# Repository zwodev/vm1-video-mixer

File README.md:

# VM-1 / The Video Mixer for Everyone

The VM-1 is an open-source hardware project for live mixing of videos, camera images and generative graphics. It is based on the widely used and affordable Raspberry Pi (5) platform, allowing creative media projects of all sorts.

Learn more about the VM-1 on our website: [VM-1 Website](https://vm-1.com)

## 🚀 Quick Start

You want to build your very own VM-1?! Awesome! This is how you do it:

### 1. Order the Parts
You're lucky! We've prepared a shopping list for you. This is a link to the shopping cart at BerryBase (Berlin, Germany). You don't have to buy the parts there and this is no affiliate link. It's just for your convenience!
This list includes everything you need. If you already own some parts, just delete them from the cart.

[Shopping List](https://www.berrybase.de/loadBasket/sqdnehV_owC)

### 2. Print your Case
Don't worry, you do not have wildly connect all the parts. We've prepared a neat little housing for your VM-1. You just have to print it on your own, your friend's or your makerspace's 3D-printer. If you have trouble getting your case printed, don't worry and drop us a line.

[3D Printing Files](#)

### 3. Download VM-1 image and flash your SD card
TODO

### 4. Assemble the VM-1
TODO

### 5. First Steps
TODO

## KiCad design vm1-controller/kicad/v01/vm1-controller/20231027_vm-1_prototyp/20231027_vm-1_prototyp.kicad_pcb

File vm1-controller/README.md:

# VM-1 Controller

folders:

`arduino` - latest firmware

`firmware`- was a test and is obsolete

`kicad`- the latest pcb

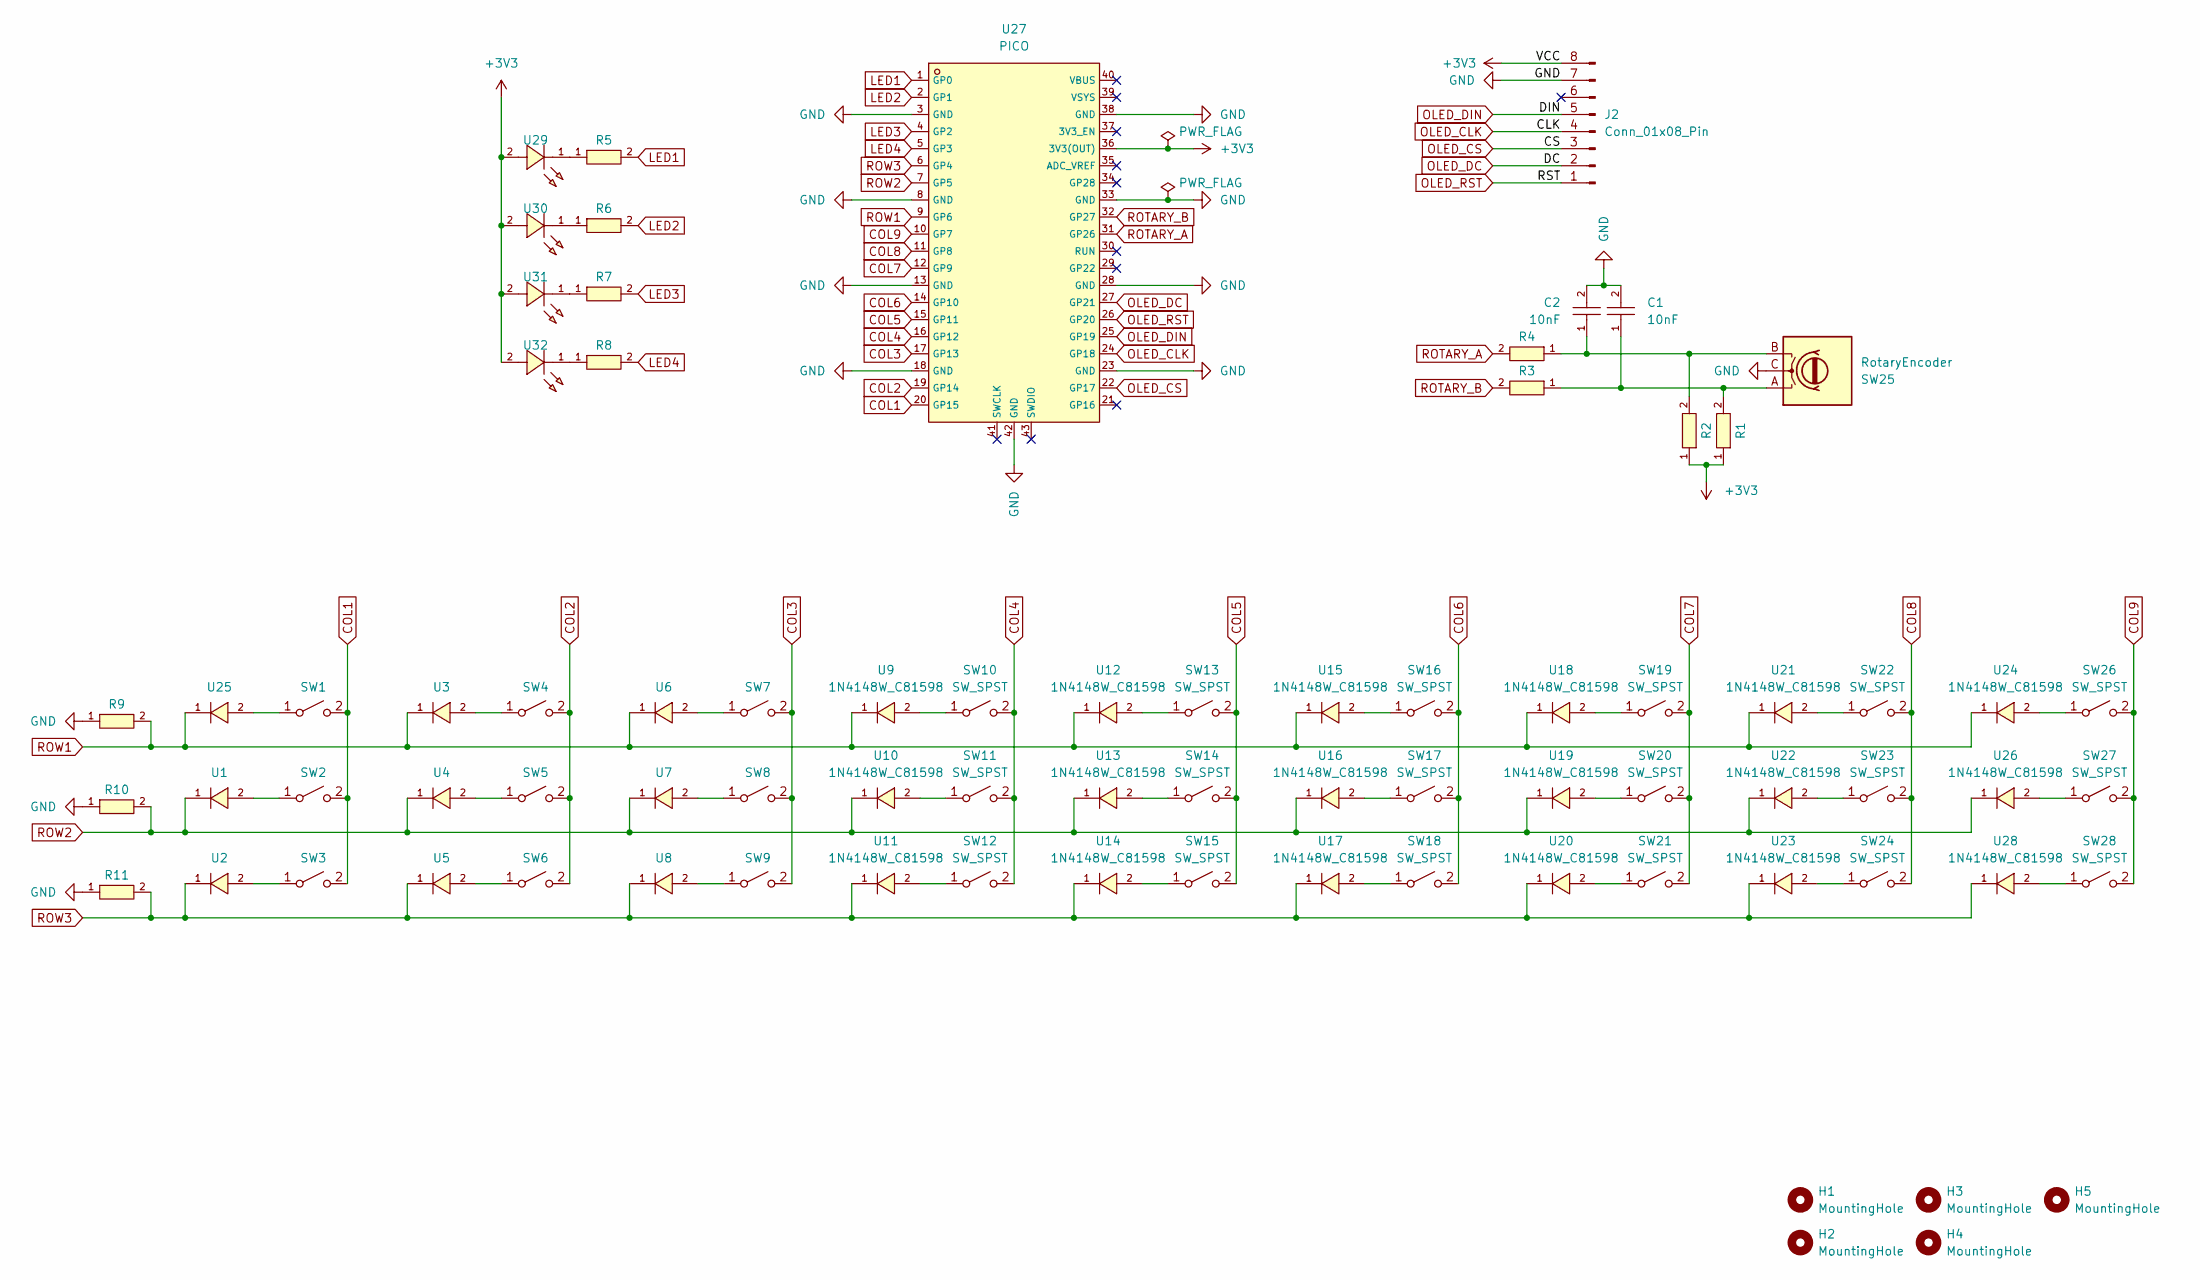
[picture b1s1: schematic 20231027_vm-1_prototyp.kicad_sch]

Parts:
C1, C2: 10nF; C0402; LCSC C15195
H1, H2, H3, H4, H5: MountingHole; MountingHole_3.2mm_M3
J2: Conn_01x08_Pin; Waveshare OLED 1.5in
R1, R2, R9, R10, R11: 0402WGF1002TCE; R0402; LCSC C25744
R3, R4: 0402WGF1002TCE 10k; R0402; LCSC C25744
R5, R6, R7, R8: 0402WGF1000TCE; R0402; LCSC C25076
SW1, SW2, SW3, SW4, SW5, SW6, SW7, SW8, SW9, SW10, SW11, SW12, SW13, SW14, SW15, SW16, SW17, SW18, SW19, SW20, SW21, SW22, SW23, SW24, SW26, SW27, SW28: SW_SPST; SW_Cherry_MX_PCB_1.00u
SW25: RotaryEncoder; RotaryEncoder_Bourns_Vertical_PEC12R-3xxxF-Nxxxx
U1, U2, U3, U4, U5, U6, U7, U8, U9, U10, U11, U12, U13, U14, U15, U16, U17, U18, U19, U20, U21, U22, U23, U24, U25, U26, U28: 1N4148W_C81598; SOD-123F_L2.7-W1.6-LS3.8-RD; LCSC C81598
U27: PICO; COMM-SMD_L51.0-W21.0-P2.54_SC0916; LCSC C7203002
U29, U30, U31, U32: 95-21SURC_S530-A3_TR10; LED-SMD_L2.1-W2.0-RD; LCSC C2936535

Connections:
+3V3: J2.8, R1.1, R2.1, U27.36 (3V3(OUT)), U29.2 (A), U30.2 (A), U31.2 (A), U32.2 (A)
COL1: SW1.2 (B), SW2.2 (B), SW3.2 (B), U27.20 (GP15)
COL2: SW4.2 (B), SW5.2 (B), SW6.2 (B), U27.19 (GP14)
COL3: SW7.2 (B), SW8.2 (B), SW9.2 (B), U27.17 (GP13)
COL4: SW10.2 (B), SW11.2 (B), SW12.2 (B), U27.16 (GP12)
COL5: SW13.2 (B), SW14.2 (B), SW15.2 (B), U27.15 (GP11)
COL6: SW16.2 (B), SW17.2 (B), SW18.2 (B), U27.14 (GP10)
COL7: SW19.2 (B), SW20.2 (B), SW21.2 (B), U27.12 (GP9)
COL8: SW22.2 (B), SW23.2 (B), SW24.2 (B), U27.11 (GP8)
COL9: SW26.2 (B), SW27.2 (B), SW28.2 (B), U27.10 (GP7)
GND: C1.2, C2.2, J2.7, R9.1, R10.1, R11.1, SW25.C, U27.3 (GND), U27.8 (GND), U27.13 (GND), U27.18 (GND), U27.23 (GND), U27.28 (GND), U27.33 (GND), U27.38 (GND), U27.42 (GND)
LED1: R5.2, U27.1 (GP0)
LED2: R6.2, U27.2 (GP1)
LED3: R7.2, U27.4 (GP2)
LED4: R8.2, U27.5 (GP3)
unnamed: C1.1, R1.2, R3.1, SW25.A
unnamed: C2.1, R2.2, R4.1, SW25.B
unnamed: SW1.1 (A), U25.2 (A)
unnamed: SW2.1 (A), U1.2 (A)
unnamed: SW3.1 (A), U2.2 (A)
unnamed: SW4.1 (A), U3.2 (A)
unnamed: SW5.1 (A), U4.2 (A)
unnamed: SW6.1 (A), U5.2 (A)
unnamed: SW7.1 (A), U6.2 (A)
unnamed: SW8.1 (A), U7.2 (A)
unnamed: SW9.1 (A), U8.2 (A)
unnamed: SW10.1 (A), U9.2 (A)
unnamed: SW11.1 (A), U10.2 (A)
unnamed: SW12.1 (A), U11.2 (A)
unnamed: SW13.1 (A), U12.2 (A)
unnamed: SW14.1 (A), U13.2 (A)
unnamed: SW15.1 (A), U14.2 (A)
unnamed: SW16.1 (A), U15.2 (A)
unnamed: SW17.1 (A), U16.2 (A)
unnamed: SW18.1 (A), U17.2 (A)
unnamed: SW19.1 (A), U18.2 (A)
unnamed: SW20.1 (A), U19.2 (A)
unnamed: SW21.1 (A), U20.2 (A)
unnamed: SW22.1 (A), U21.2 (A)
unnamed: SW23.1 (A), U22.2 (A)
unnamed: SW24.1 (A), U23.2 (A)
unnamed: SW26.1 (A), U24.2 (A)
unnamed: SW27.1 (A), U26.2 (A)
unnamed: SW28.1 (A), U28.2 (A)
unnamed: R5.1, U29.1 (K)
unnamed: R6.1, U30.1 (K)
unnamed: R7.1, U31.1 (K)
unnamed: R8.1, U32.1 (K)
OLED_CLK: J2.4, U27.24 (GP18)
OLED_CS: J2.3, U27.22 (GP17)
OLED_DC: J2.2, U27.27 (GP21)
OLED_DIN: J2.5, U27.25 (GP19)
OLED_RST: J2.1, U27.26 (GP20)
ROTARY_A: R4.2, U27.31 (GP26)
ROTARY_B: R3.2, U27.32 (GP27)
ROW1: R9.2, U3.1 (K), U6.1 (K), U9.1 (K), U12.1 (K), U15.1 (K), U18.1 (K), U21.1 (K), U24.1 (K), U25.1 (K), U27.9 (GP6)
ROW2: R10.2, U1.1 (K), U4.1 (K), U7.1 (K), U10.1 (K), U13.1 (K), U16.1 (K), U19.1 (K), U22.1 (K), U26.1 (K), U27.7 (GP5)
ROW3: R11.2, U2.1 (K), U5.1 (K), U8.1 (K), U11.1 (K), U14.1 (K), U17.1 (K), U20.1 (K), U23.1 (K), U27.6 (GP4), U28.1 (K)

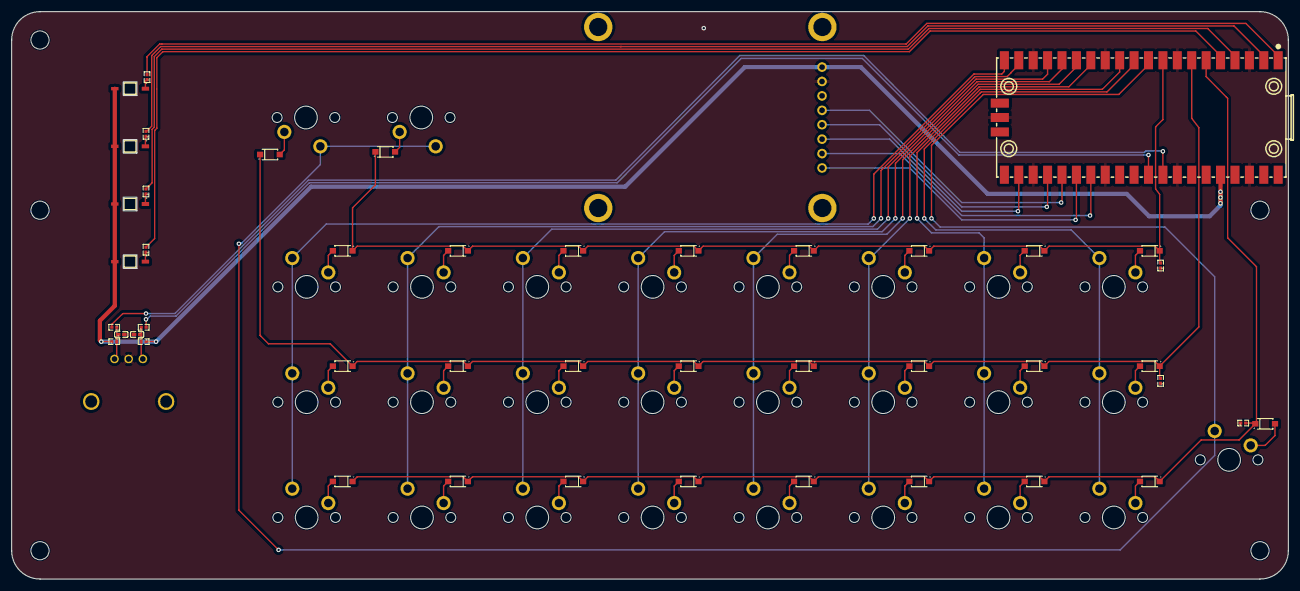
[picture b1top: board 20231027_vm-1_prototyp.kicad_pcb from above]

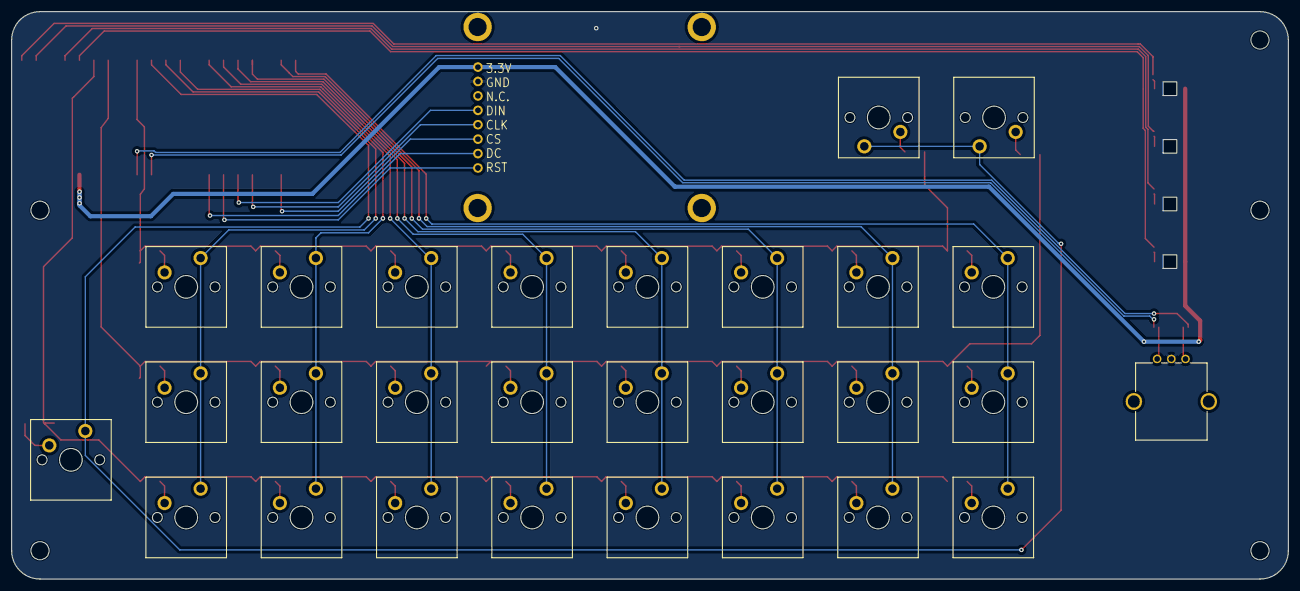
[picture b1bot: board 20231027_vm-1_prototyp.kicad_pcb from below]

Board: 2 copper layers, 225.0 x 100.0 mm, 79 parts (29 on the bottom side), 58 nets.

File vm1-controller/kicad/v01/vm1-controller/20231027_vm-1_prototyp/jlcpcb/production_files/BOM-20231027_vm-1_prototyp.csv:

Comment,Designator,Footprint,LCSC
10nF,"C1,C2",C0402,C15195
0402WGF1000TCE,"R5,R6,R7,R8",R0402,C25076
0402WGF1002TCE,"R1,R10,R11,R2,R3,R4,R9",R0402,C25744
95-21SURC_S530-A3_TR10,"U29,U30,U31,U32",LED-SMD_L2.1-W2.0-RD,C2936535
PICO,U27,COMM-SMD_L51.0-W21.0-P2.54_SC0916,C7203002
1N4148W_C81598,"U1,U10,U11,U12,U13,U14,U15,U16,U17,U18,U19,U2,U20,U21,U22,U23,U24,U25,U26,U28,U3,U4,U5,U6,U7,U8,U9",SOD-123F_L2.7-W1.6-LS3.8-RD,C81598
SW_SPST,SW27,SW_Cherry_MX_PCB_1.00u,
SW_SPST,SW28,SW_Cherry_MX_PCB_1.00u,
SW_SPST,SW20,SW_Cherry_MX_PCB_1.00u,
SW_SPST,SW16,SW_Cherry_MX_PCB_1.00u,
SW_SPST,SW24,SW_Cherry_MX_PCB_1.00u,
SW_SPST,SW9,SW_Cherry_MX_PCB_1.00u,
RotaryEncoder,SW25,RotaryEncoder_Bourns_Vertical_PEC12R-3xxxF-Nxxxx,
SW_SPST,SW15,SW_Cherry_MX_PCB_1.00u,
SW_SPST,SW2,SW_Cherry_MX_PCB_1.00u,
SW_SPST,SW7,SW_Cherry_MX_PCB_1.00u,
SW_SPST,SW11,SW_Cherry_MX_PCB_1.00u,
SW_SPST,SW8,SW_Cherry_MX_PCB_1.00u,
SW_SPST,SW12,SW_Cherry_MX_PCB_1.00u,
SW_SPST,SW1,SW_Cherry_MX_PCB_1.00u,
SW_SPST,SW17,SW_Cherry_MX_PCB_1.00u,
SW_SPST,SW10,SW_Cherry_MX_PCB_1.00u,
SW_SPST,SW22,SW_Cherry_MX_PCB_1.00u,
SW_SPST,SW14,SW_Cherry_MX_PCB_1.00u,
SW_SPST,SW6,SW_Cherry_MX_PCB_1.00u,
Conn_01x08_Pin,J2,Waveshare OLED 1.5in,
SW_SPST,SW21,SW_Cherry_MX_PCB_1.00u,
SW_SPST,SW26,SW_Cherry_MX_PCB_1.00u,
SW_SPST,SW4,SW_Cherry_MX_PCB_1.00u,
SW_SPST,SW19,SW_Cherry_MX_PCB_1.00u,
SW_SPST,SW5,SW_Cherry_MX_PCB_1.00u,
SW_SPST,SW23,SW_Cherry_MX_PCB_1.00u,
SW_SPST,SW13,SW_Cherry_MX_PCB_1.00u,
SW_SPST,SW3,SW_Cherry_MX_PCB_1.00u,
SW_SPST,SW18,SW_Cherry_MX_PCB_1.00u,

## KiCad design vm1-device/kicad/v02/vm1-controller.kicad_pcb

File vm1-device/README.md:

# VM-1 Controller

`arduino` - firmware

`kicad`- pcb

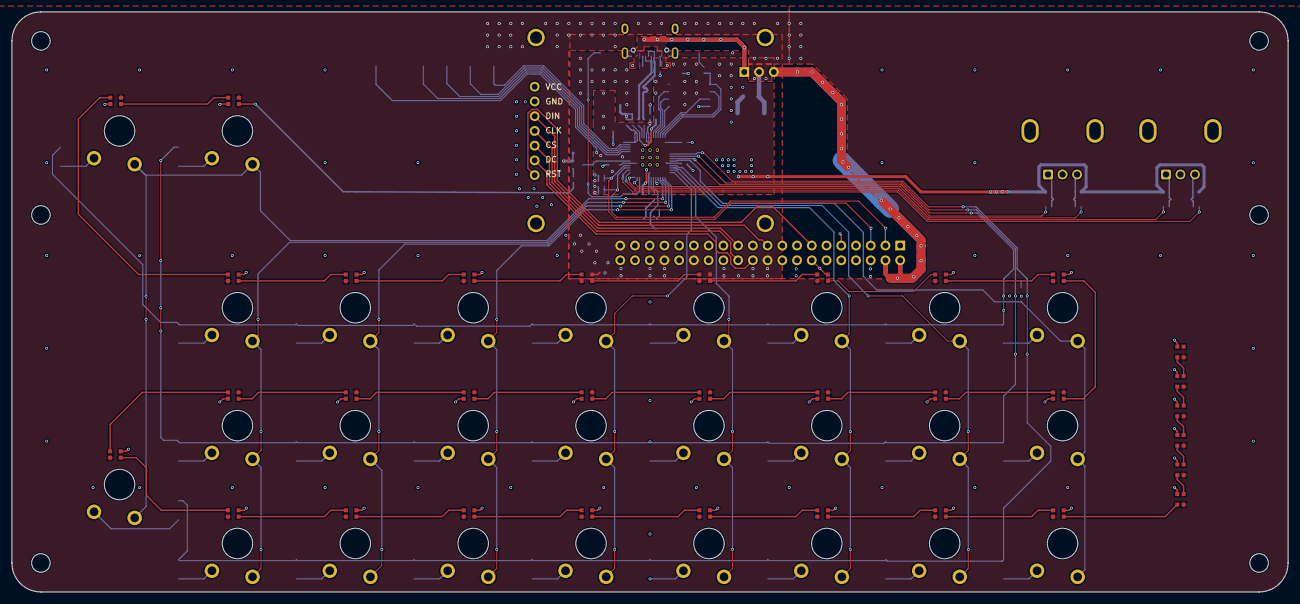
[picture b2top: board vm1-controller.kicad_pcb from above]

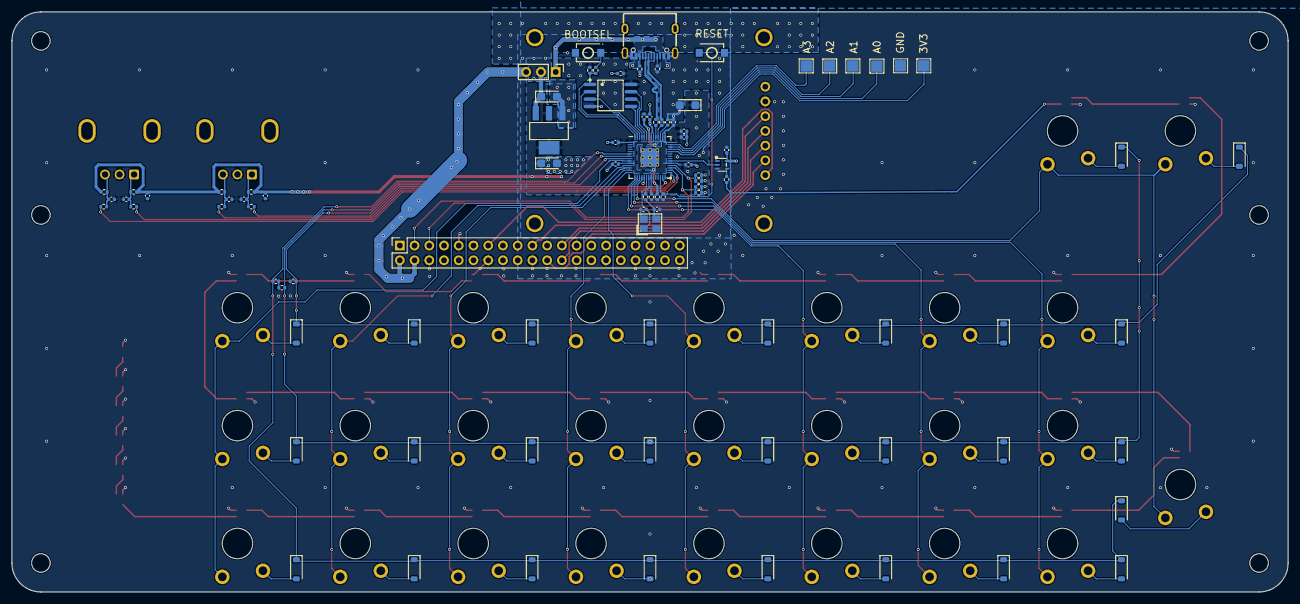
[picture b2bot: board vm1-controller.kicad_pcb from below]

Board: 4 copper layers, 220.0 x 100.0 mm, 160 parts (91 on the bottom side), 117 nets.

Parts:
3.3V1: 3.3V; TestPoint_Pad_2.0x2.0mm
ADC_0: ADC_0; TestPoint_Pad_2.0x2.0mm
ADC_1: ADC_1; TestPoint_Pad_2.0x2.0mm
ADC_2: ADC_2; TestPoint_Pad_2.0x2.0mm
ADC_3: ADC_3; TestPoint_Pad_2.0x2.0mm
C1, C2, C3, C4: 10n; C_0402_1005Metric
C5, C6, C7, C9, C11, C12, C13, C14, C15, C16, C22, C25: 100n; C_0402_1005Metric
C8, C10, C23, C24: 1u; C_0402_1005Metric
C17, C18: 15p; C_0402_1005Metric
C19, C20, C21: 10u; CP_EIA-3216-10_Kemet-I
D1, D2, D3, D4, D5, D6, D7, D8, D9, D10, D11, D12, D13, D14, D15, D16, D17, D18, D19, D20, D21, D22, D23, D24, D25, D26, D27, D28, D29, D30, D31, D32, D33: WS2812B-2020; LED_WS2812B-2020_PLCC4_2.0x2.0mm
GND1: GND; TestPoint_Pad_2.0x2.0mm
H1, H2, H3, H4, H5, H22: MountingHole; MountingHole_3.2mm_M3
J1: Raspberry_Pi_5_GPIO; PinSocket_2x20_P2.54mm_Vertical
J3: Conn_01x07_Pin; Waveshare-OLED-RGB-1.5in
JP1: 5V power selector; PinHeader_1x03_P2.54mm_Vertical
R1, R2, R3, R4, R5, R6, R7, R8, R9, R10, R11, R18, R20, R21, R22: 10k; R_0402_1005Metric
R12, R13, R23: 27; R_0402_1005Metric
R14: DNF; R_0402_1005Metric
R15, R16: 1k; R_0402_1005Metric
R17, R19: 5.1k; R_0402_1005Metric
SW1, SW2, SW3, SW4, SW5, SW6, SW7, SW8, SW9, SW10, SW11, SW12, SW13, SW14, SW15, SW16, SW17, SW18, SW19, SW20, SW21, SW22, SW23, SW24, SW26, SW27, SW28: SW_SPST; SW_Gateron_LowProfile_THT
SW25, SW29: RotaryEncoder; RotaryEncoder_Bourns_Vertical_PEC12R-3x17F-Nxxxx
U1, U2, U3, U4, U5, U6, U7, U8, U9, U10, U11, U12, U13, U14, U15, U16, U17, U18, U19, U20, U21, U22, U23, U24, U25, U26, U28: 1N4148W_C81598; D_SOD-123
U27: 74LVC1G17GW,125_C426705; SOT-353_L2.1-W1.3-P0.65-LS2.3-BR
U29: AMS1117-3_3; SOT-223-3_L6.5-W3.4-P2.30-LS7.0-BR
U30: RP2040; RP2040-QFN-56
U31: TYPE-C_16PIN_2MD(073); USB-C-SMD_TYPE-C-6PIN-2MD-073
U32: W25Q128JVSIQTR; SOIC-8_L5.3-W5.3-P1.27-LS8.0-BL
U33, U34: TS-1088-AR02016; SW-SMD_L3.9-W3.0-P4.45
X2: ABM8-272-T3_C20625731; CRYSTAL-SMD_4P-L3.2-W2.5-BL

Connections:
+1V1: C6.1, C7.1, C8.1, U30.23 (DVDD), U30.45 (VREG_VOUT), U30.50 (DVDD)
+3V3: 3.3V1.1, C5.1, C9.1, C10.1, C11.1, C12.1, C13.1, C14.1, C15.1, C16.1, C19.1, C21.1, C23.1, C24.1, R1.1, R2.1, R7.1, R8.1, R14.1, R18.1, R20.1, R21.1, R22.1, U29.2 (VOUT), U29.4 (VOUT), U30.1 (IOVDD), U30.10 (IOVDD), U30.22 (IOVDD), U30.33 (IOVDD), U30.42 (IOVDD), U30.43 (ADC_AVDD), U30.44 (VREG_IN), U30.48 (USB_VDD), U30.49 (IOVDD), U32.8 (VCC)
+3V3_RPI: J1.1 (3V3), J1.17 (3V3), J3.7
+5V: C20.1, C25.1, D1.4 (VDD), D2.4 (VDD), D3.4 (VDD), D4.4 (VDD), D5.4 (VDD), D6.4 (VDD), D7.4 (VDD), D8.4 (VDD), D9.4 (VDD), D10.4 (VDD), D11.4 (VDD), D12.4 (VDD), D13.4 (VDD), D14.4 (VDD), D15.4 (VDD), D16.4 (VDD), D17.4 (VDD), D18.4 (VDD), D19.4 (VDD), D20.4 (VDD), D21.4 (VDD), D22.4 (VDD), D23.4 (VDD), D24.4 (VDD), D25.4 (VDD), D26.4 (VDD), D27.4 (VDD), D28.4 (VDD), D29.4 (VDD), D30.4 (VDD), D31.4 (VDD), D32.4 (VDD), D33.4 (VDD), JP1.2 (C), U27.5 (VCC), U29.3 (VIN)
+5V_RPI: J1.2 (5V), J1.4 (5V), JP1.3 (B)
+5V_USB: JP1.1 (A), U31.2 (VBUS), U31.11 (VBUS)
/COL1: SW1.2 (B), SW2.2 (B), SW3.2 (B), U30.9 (GPIO7)
/COL2: SW4.2 (B), SW5.2 (B), SW6.2 (B), U30.11 (GPIO8)
/COL3: SW7.2 (B), SW8.2 (B), SW9.2 (B), U30.12 (GPIO9)
/COL4: SW10.2 (B), SW11.2 (B), SW12.2 (B), U30.13 (GPIO10)
/COL5: SW13.2 (B), SW14.2 (B), SW15.2 (B), U30.14 (GPIO11)
/COL6: SW16.2 (B), SW17.2 (B), SW18.2 (B), U30.15 (GPIO12)
/COL7: SW19.2 (B), SW20.2 (B), SW21.2 (B), U30.16 (GPIO13)
/COL8: SW22.2 (B), SW23.2 (B), SW24.2 (B), U30.17 (GPIO14)
/COL9: SW26.2 (B), SW27.2 (B), SW28.2 (B), U30.18 (GPIO15)
/I2C_SCL: J1.5 (SCL_I2C1/GPIO03), R18.2, R21.2, U30.32 (GPIO21)
/I2C_SDA: J1.3 (SDA_I2C1/GPIO02), R20.2, R22.2, U30.31 (GPIO20)
/OLED_SPI_CLK: J1.23 (SCLK_SPI0/GPIO11), J3.4
/OLED_SPI_CS: J1.24 (~CE0_SPI0/GPIO08), J3.3
/OLED_SPI_DC: J1.22 (GPIO25/SDIO_DAT1), J3.2
/OLED_SPI_DIN: J1.19 (MOSI_SPI0/GPIO10), J3.5
/OLED_SPI_RST: J1.13 (GPIO27/SDIO_DAT3), J3.1
/Pi Pico 2040/GPIO26_ADC0: ADC_0.1, U30.38 (GPIO26_ADC0)
/Pi Pico 2040/GPIO27_ADC1: ADC_1.1, U30.39 (GPIO27_ADC1)
/Pi Pico 2040/GPIO28_ADC2: ADC_2.1, U30.40 (GPIO28_ADC2)
/Pi Pico 2040/GPIO29_ADC3: ADC_3.1, U30.41 (GPIO29_ADC3)
/Pi Pico 2040/QSPI_SCLK: U30.52 (QSPI_SCLK), U32.6 (CLK)
/Pi Pico 2040/QSPI_SD0: U30.53 (QSPI_SD0), U32.5 (DI)
/Pi Pico 2040/QSPI_SD1: U30.55 (QSPI_SD1), U32.2 (DO)
/Pi Pico 2040/QSPI_SD2: U30.54 (QSPI_SD2), U32.3 (IO2)
/Pi Pico 2040/QSPI_SD3: U30.51 (QSPI_SD3), U32.7 (IO3)
/Pi Pico 2040/QSPI_SS: R14.2, R15.1, U30.56 (QSPI_SS), U32.1 (CS#)
/Pi Pico 2040/RUN: C22.2, U30.26 (RUN), U34.2
/Pi Pico 2040/USB_D+: R12.1, U31.6 (DP1), U31.8 (DP2)
/Pi Pico 2040/USB_D-: R13.1, U31.5 (DN2), U31.7 (DN1)
/Pi Pico 2040/XIN: C17.1, U30.20 (XIN), X2.1
/Pi Pico 2040/XOUT: R16.1, U30.21 (XOUT)
/Pi Pico 2040/~USB_BOOT: R15.2, U33.2
/ROTARY_1_A: R4.2, U30.28 (GPIO17)
/ROTARY_1_B: R3.2, U30.27 (GPIO16)
/ROTARY_2_A: R5.2, U30.30 (GPIO19)
/ROTARY_2_B: R6.2, U30.29 (GPIO18)
/ROW1: R9.2, U3.1 (K), U6.1 (K), U9.1 (K), U12.1 (K), U15.1 (K), U18.1 (K), U21.1 (K), U24.1 (K), U25.1 (K), U30.8 (GPIO6)
/ROW2: R10.2, U1.1 (K), U4.1 (K), U7.1 (K), U10.1 (K), U13.1 (K), U16.1 (K), U19.1 (K), U22.1 (K), U26.1 (K), U30.7 (GPIO5)
/ROW3: R11.2, U2.1 (K), U5.1 (K), U8.1 (K), U11.1 (K), U14.1 (K), U17.1 (K), U20.1 (K), U23.1 (K), U28.1 (K), U30.6 (GPIO4)
/WS2812B: U27.2 (A), U30.34 (GPIO22)
GND: C1.2, C2.2, C3.2, C4.2, C5.2, C6.2, C7.2, C8.2, C9.2, C10.2, C11.2, C12.2, C13.2, C14.2, C15.2, C16.2, C17.2, C18.2, C19.2, C20.2, C21.2, C22.1, C23.2, C24.2, C25.2, D1.2 (VSS), D2.2 (VSS), D3.2 (VSS), D4.2 (VSS), D5.2 (VSS), D6.2 (VSS), D7.2 (VSS), D8.2 (VSS), D9.2 (VSS), D10.2 (VSS), D11.2 (VSS), D12.2 (VSS), D13.2 (VSS), D14.2 (VSS), D15.2 (VSS), D16.2 (VSS), D17.2 (VSS), D18.2 (VSS), D19.2 (VSS), D20.2 (VSS), D21.2 (VSS), D22.2 (VSS), D23.2 (VSS), D24.2 (VSS), D25.2 (VSS), D26.2 (VSS), D27.2 (VSS), D28.2 (VSS), D29.2 (VSS), D30.2 (VSS), D31.2 (VSS), D32.2 (VSS), D33.2 (VSS), GND1.1, J1.6 (GND), J1.9 (GND), J1.14 (GND), J1.20 (GND), J1.25 (GND), J1.30 (GND), J1.34 (GND), J1.39 (GND), J3.6, R9.1, R10.1, R11.1, R17.1, R19.1, SW25.C, SW29.C, U27.3 (GND), U29.1 (GND), U30.19 (TESTEN), U30.57 (GND), U31.1 (GND), U31.12 (GND), U31.13 (SHELL), U31.14 (SHELL), U32.4 (GND), U33.1, U34.1, X2.2 (GND), X2.4 (GND)
unnamed: C1.1, R1.2, R3.1, SW25.A
unnamed: C2.1, R2.2, R4.1, SW25.B
unnamed: C3.1, R5.1, R7.2, SW29.B
unnamed: C4.1, R6.1, R8.2, SW29.A
unnamed: C18.1, R16.2, X2.3
unnamed: D1.3 (DIN), D25.1 (DOUT)
unnamed: D1.1 (DOUT), D2.3 (DIN)
unnamed: D2.1 (DOUT), D3.3 (DIN)
unnamed: D3.1 (DOUT), D4.3 (DIN)
unnamed: D4.1 (DOUT), D5.3 (DIN)
unnamed: D5.1 (DOUT), D6.3 (DIN)
unnamed: D6.1 (DOUT), D7.3 (DIN)
unnamed: D7.1 (DOUT), D8.3 (DIN)
unnamed: D8.1 (DOUT), D9.3 (DIN)
unnamed: D9.1 (DOUT), D10.3 (DIN)
unnamed: D10.1 (DOUT), D11.3 (DIN)
unnamed: D11.1 (DOUT), D12.3 (DIN)
unnamed: D12.1 (DOUT), D13.3 (DIN)
unnamed: D13.1 (DOUT), D14.3 (DIN)
unnamed: D14.1 (DOUT), D15.3 (DIN)
unnamed: D15.1 (DOUT), D16.3 (DIN)
unnamed: D16.1 (DOUT), D27.3 (DIN)
unnamed: D17.3 (DIN), D27.1 (DOUT)
unnamed: D17.1 (DOUT), D18.3 (DIN)
unnamed: D18.1 (DOUT), D19.3 (DIN)
unnamed: D19.1 (DOUT), D20.3 (DIN)
unnamed: D20.1 (DOUT), D21.3 (DIN)
unnamed: D21.1 (DOUT), D22.3 (DIN)
unnamed: D22.1 (DOUT), D23.3 (DIN)
unnamed: D23.1 (DOUT), D24.3 (DIN)
unnamed: D24.1 (DOUT), D28.3 (DIN)
unnamed: D25.3 (DIN), D26.1 (DOUT)
unnamed: D26.3 (DIN), R23.1
unnamed: D28.1 (DOUT), D29.3 (DIN)
unnamed: D29.1 (DOUT), D30.3 (DIN)
unnamed: D30.1 (DOUT), D31.3 (DIN)
unnamed: D31.1 (DOUT), D32.3 (DIN)
unnamed: D32.1 (DOUT), D33.3 (DIN)
unnamed: SW1.1 (A), U25.2 (A)
unnamed: SW2.1 (A), U1.2 (A)
unnamed: SW3.1 (A), U2.2 (A)
unnamed: SW4.1 (A), U3.2 (A)
unnamed: SW5.1 (A), U4.2 (A)
unnamed: SW6.1 (A), U5.2 (A)
unnamed: SW7.1 (A), U6.2 (A)
unnamed: SW8.1 (A), U7.2 (A)
unnamed: SW9.1 (A), U8.2 (A)
unnamed: SW10.1 (A), U9.2 (A)
unnamed: SW11.1 (A), U10.2 (A)
unnamed: SW12.1 (A), U11.2 (A)
unnamed: SW13.1 (A), U12.2 (A)
unnamed: SW14.1 (A), U13.2 (A)
unnamed: SW15.1 (A), U14.2 (A)
unnamed: SW16.1 (A), U15.2 (A)
unnamed: SW17.1 (A), U16.2 (A)
unnamed: SW18.1 (A), U17.2 (A)
unnamed: SW19.1 (A), U18.2 (A)
unnamed: SW20.1 (A), U19.2 (A)
unnamed: SW21.1 (A), U20.2 (A)
unnamed: SW22.1 (A), U21.2 (A)
unnamed: SW23.1 (A), U22.2 (A)
unnamed: SW24.1 (A), U23.2 (A)
unnamed: SW26.1 (A), U24.2 (A)
unnamed: SW27.1 (A), U26.2 (A)
unnamed: SW28.1 (A), U28.2 (A)
unnamed: R23.2, U27.4 (Y)
unnamed: R13.2, U30.46 (USB_DM)
unnamed: R12.2, U30.47 (USB_DP)
unnamed: R19.2, U31.4 (CC1)
unnamed: R17.2, U31.10 (CC2)

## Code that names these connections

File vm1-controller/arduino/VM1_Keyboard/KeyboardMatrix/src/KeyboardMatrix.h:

#ifndef KEYBOARDMATRIX_H
#define KEYBOARDMATRIX_H

#include "Keyboard.h"

// input rows pins
#define ROW1 6
#define ROW2 5
#define ROW3 4

// output colums pins
#define COL1 7
#define COL2 8
#define COL3 9
#define COL4 10
#define COL5 11
#define COL6 12
#define COL7 13
#define COL8 14
#define COL9 15

#define PRESSED 0
#define RELEASED 1

void init_keyboard();
void check_keyboard_matrix();
void update_keyboard();
void set_keyboard_buffer(char* buffer, uint8_t size, bool* shiftkey);
void clear_keyboard_buffer();
void add_to_keyboard_buffer(char c);

#endif

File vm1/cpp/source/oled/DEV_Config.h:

#ifndef _DEV_CONFIG_H_
#define _DEV_CONFIG_H_
/***********************************************************************************************************************
            ------------------------------------------------------------------------
            |\\\																///|
            |\\\					Hardware interface							///|
            ------------------------------------------------------------------------
***********************************************************************************************************************/
#ifdef __cplusplus
extern "C"
{
#endif

#include "Debug.h"
#ifdef USE_BCM2835_LIB
#include <bcm2835.h>
#elif USE_WIRINGPI_LIB
#include <wiringPi.h>
#include <wiringPiSPI.h>
#include <wiringPiI2C.h>
#elif USE_DEV_LIB
#include <lgpio.h>
#define LFLAGS 0
#define NUM_MAXBUF 4
#endif

#include <errno.h>
#include <stdio.h>
#include <string.h>
#include <stdint.h>
#include <unistd.h>

#define USE_SPI 1
#define USE_IIC 0

#define IIC_CMD 0X00
#define IIC_RAM 0X40

/**
 * data
 **/
#define UBYTE uint8_t
#define UWORD uint16_t
#define UDOUBLE uint32_t

// OLED Define
#define OLED_CS 8
#define OLED_RST 27
#define OLED_DC 25

#define OLED_CS_0 DEV_Digital_Write(OLED_CS, 0)
#define OLED_CS_1 DEV_Digital_Write(OLED_CS, 1)

#define OLED_RST_0 DEV_Digital_Write(OLED_RST, 0)
#define OLED_RST_1 DEV_Digital_Write(OLED_RST, 1)

#define OLED_DC_0 DEV_Digital_Write(OLED_DC, 0)
#define OLED_DC_1 DEV_Digital_Write(OLED_DC, 1)

    /*------------------------------------------------------------------------------------------------------*/

    UBYTE DEV_ModuleInit(void);
    void DEV_ModuleExit(void);

    void DEV_GPIO_Mode(UWORD Pin, UWORD Mode);
    void DEV_Digital_Write(UWORD Pin, UBYTE Value);
    UBYTE DEV_Digital_Read(UWORD Pin);
    void DEV_Delay_ms(UDOUBLE xms);

    void I2C_Write_Byte(uint8_t value, uint8_t Cmd);
    int DEV_SPI_WriteByte(UBYTE Value);
    int DEV_SPI_Write_nByte(uint8_t *pData, uint32_t Len);

#ifdef __cplusplus
}
#endif

#endif

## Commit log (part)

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2023-11-28 PlaneRenderer works now.
2023-11-28 Added hevc testvideo.
2024-04-01 Fixed links in header comments and README.
2025-02-05 Added fetch script for test videos.
2025-02-05 Implemented threaded video decoding (WIP).
2025-02-05 Minor changes.
2025-02-12 Added video plane. Optimizations.
2025-02-14 Performance optimizations.
2025-02-25 Added HDMI2CSI adapter config scripts.
2025-02-25 Added FileAssignmentWidget.
2025-02-25 Modified README.md file.
2025-02-26 initial commit clockdiv
    - first prototype of the vm-1 pcb (hardware, firmware)
    - 3d file for prototype baseplate
2025-02-26 Added keyboard shortcuts.
2025-02-26 Clean-up.
2025-02-27 Videos play in realtime now (added PTS check).
2025-02-27 Added V4L2Controller class.
2025-02-28 Added CameraController (WIP).
2025-02-28 Added OledController (WIP).
2025-02-28 OLED Display initial commit
2025-03-01 Added OledUiRenderer class (FBO).
2025-03-14 added OLED display
2025-03-14 test app for oled gui
2025-03-19 vm-1 keyboard prototype
    added keyboard-press and -release
2025-03-19 Added KeyForwarder class.
2025-03-20 imgui oled menu
2025-03-20 added EDID files for hdmi input
2025-03-21 Changed to C++23 and started transition to smart pointers.
2025-03-21 FileAssignmentWidget works with Registry now.
2025-03-21 Add UIHelper.
2025-03-31 KeyAssignment
2025-04-02 UI, Menu and Buttons
2025-04-03 Added threading to OLED routines.
2025-04-15 Added HDMI mixing and localsend install script.
2025-04-15 Added filter for hdmi dummy file for testing.
2025-04-18 Extracted getBuffer from lockBuffer in CameraPlayer.
2025-04-18 Removed unlockBuffer in VideoPlane.
2025-04-18 added infoscreen and settings-menu mockups
2025-04-19 Added looping to VideoPlayer.
2025-04-20 Refined MenuSystem and Registry.
2025-04-21 Correct navigation in dynamic menus.
2025-04-22 Tweaking and clean-up.
2025-04-29 Fixed HDMI playing issue and setup EDID on start.
2025-05-05 Added serialization to registry.
2025-05-07 first test for messagepack-communication
2025-05-13 added compile script
2025-05-13 changes in README.md
2025-05-15 Added new classes.
2025-05-15 Added PlaybackOperator and refactoring.
2025-05-15 UI improvements, bug-fixing and hashing registry snapshots.
2025-05-16 keyboard controller works
2025-05-16 Fix VideoPlayer (isPlaying).
2025-05-16 sorted filenames
2025-05-16 Fixed segfault.
2025-05-16 Removed file filters.
2025-05-17 Bank switching works (with led indicators), auto-save works.
2025-05-17 Added Network info screen (edit button 7).
2025-05-17 Call updateVideoFiles in getVideoFiles as temp solution.
2025-05-31 Quick fix for letterboxed mode.
2025-06-03 Added check for HEVC/1080p for VideoPlayer.
2025-06-07 Added compute shader test.
2025-06-12 mediaslot with Bank+ID in OLED-Display
2025-06-12 i2c test
2025-06-12 changes in readme
2025-06-12 rotary encoder library
2025-06-13 VM-1 Controller V2.0
    ordered at jlcpcb
2025-06-25 stb font rendering test
2025-06-30 Updated Shader class.
2025-07-02 Optimizations and clean-up.
2025-07-02 Added vert.pass to compute-shader test.
2025-07-02 Deleted deprecated shaders.
2025-07-02 Showing active media slots seems to work.
2025-07-08 update VM-1 controller to PCB v2
2025-07-08 VM-1 Controller clean-up
2025-07-14 SPI now on gpiochip 0.
2025-07-14 Integration of StbRenderer
2025-07-14 StbRenderer integration works (WIP).
2025-07-17 Font rendering with baseline as reference.
2025-07-17 EventSystem WIP
2025-07-17 Added deploy folder for rpi-image-gen.
2025-07-18 board connector
    connects io-board with vm1-device
2025-07-21 UI Event System working
2025-07-22 Added VM1Application class (WIP).
2025-07-23 Headless mode and video mode reinit work.
2025-07-24 OLED menu works in headless mode.
2025-07-24 PlaybackOperator and FileAssignmentWidget now use the event bus.
2025-07-24 VM1-Device update to pcb v2
2025-07-24 Fixed: Playback indicator only showing on bank 0.
2025-07-24 added i2c to KeyboardController WIP
2025-07-24 Added automatic best resolution detection and viewport setup.
2025-07-24 Fixed problem with different video resolutions and added sound (WIP).
2025-07-25 removed obsolete files from vm1-controller
2025-07-25 vm1-device minor cleanup
2025-07-25 added getTextWidth to StbRenderer
2025-07-25 DeviceController via i2c working
2025-07-25 i2c connection to vm1-device works
2025-07-25 rpi-image-gen works.
2025-07-30 UI elements
2025-07-30 DeviceController lights up selected EditButton
2025-07-30 fixed FadeTime value change with Encoder
2025-07-30 show selected (but not triggered) media button in different state/color
2025-07-30 BankInfo Overlay Renderer
2025-07-30 Recently used VideoPlayers are now closed correctly.
2025-08-01 Added valgrind suppress file.
2025-08-01 Reactivated hdmi/cam setup and fixed uninitialized struct error.
2025-08-13 Re-enabled tty output on boot for testing.
2025-08-13 Fixed: Popping fade when volume is smaller than 10.
2025-08-13 Added filter so HDR videos are not played (BT.2020).
2025-08-14 Fixed HDMI/camera shader.
2025-08-14 VM-1 Device rotary sensitivity
2025-08-14 rpi image deploy
2025-08-14 Not allowing HDR videos (colorspace BT.2020).
2025-08-18 Added reset functionality and fixed aspect ratio/resolution issues.
2025-08-19 Changed back: Use only resolutions x < 1920.
2025-08-19 fix yuv420p or yuvj420p
2025-08-19 Added KeyboardHotplug class.
2025-08-20 Reworked keyboard input and remapped edit/media keys.
2025-08-21 Added clear slot and re-arranged menus.
2025-08-21 Showing button matrix on edit button 6 now.
2025-08-25 added splash screen
2025-08-25 rpi-image deploy fix
2025-08-27 Added ImageBuffer.
2025-09-18 kiosk mode
2025-09-21 added registry entries for kiosk mode
2025-10-23 Added new class WebcamPlayer.
2025-10-24 Added error messages.
2025-10-24 WebcamPlayer implemention compiles. Needs further testing.
2025-11-04 Added webcam shader.
2025-11-20 Changed version number.
2025-12-04 Added TinyFileManager.
2025-12-22 wip prototype; use external fader
2025-12-31 added Elecrow 2.8" IPS LCD Display ILI9341
2026-02-15 Added basic shader input system.
2026-02-15 template for shadertoy, one more shader
2026-02-16 changed GPIOs for 2.8-inch-display to fit VM-1-Pro specs
2026-02-21 implemented Fn+EditButton functionality
2026-02-21 UI draft for a possible "SRC-CTRL-FX-OUT" pipeline
2026-02-23 Mapping Mode prototype
2026-02-23 Mapping Mode prototype, Arduino/DeviceController
2026-02-24 menu improvements
2026-02-24 effects integrated into menu
2026-02-26 Basic Projection Mapping
2026-02-26 Mapping Mode with SpinBoxVec2; added second rotary encoder functionality
2026-03-02 UI test for string input (still buggy, needs revision)
2026-03-03 wip event system
2026-03-03 Migrated to new event types and event mapping.
2026-03-04 Consistent controls?
2026-03-04 Mapping menu works.
2026-03-04 Screen orientation and mapping works with GLM now.
2026-03-05 added mapping for rotation, scale, translate (wip, needs fixes)
2026-03-06 Added plane selection for FX and OUT menus.
2026-03-06 Multi plane support (WIP).
2026-03-06 Not updating VideoPlayer and WebcamPlayer if not active.
2026-03-06 added planeSelection UI
2026-03-06 UI SpinBoxes return true if value has changed
2026-03-09 projection mapping preview plane in "out" menu
2026-03-09 (WIP) plane switching in ui and mapping-preview
2026-03-10 matrix calculation changes in PlaneRenderer
2026-03-10 (WIP) Mapping Mode
2026-03-11 Settings shader internal values (iTime for now) using ShaderConfig.
2026-03-11 Added simple circle shader to showcase shader parameters.
2026-03-11 Added blend mode to planes (WIP).
2026-03-12 fixed seg fault in PlaybackOperator
2026-03-12 Renamed alpha to opacity.
2026-03-12 Subfolders for custom shaders.
2026-03-12 Commented out debug strings.
2026-03-13 Blend mode multiply works with opacity value.
2026-03-13 (WIP) screenshot, menusystem
2026-03-15 multiple fonts, text-styles
2026-03-16 UI tests and refactoring
2026-03-17 added layer order indicators to UI
2026-03-17 Metadata extraction works for generative shaders.
2026-03-18 Effect shader parameters work.
2026-03-18 Show content of mini display in ImGui UI.
2026-03-19 Custom effect shaders work.
2026-03-20 UI improved overlapping text in mapping mode
2026-03-20 UI: added "hidden elements"
2026-03-20 stbRenderer: new drawImage method; UI: added gizmo to mapping mode
2026-03-26 Mirror Shader; startet with MediaPreview; fixed plane-switching
2026-03-28 extra file for MediaPool Class; Video-Preview WIP;
2026-04-02 Clean-up (no warnings).
2026-04-02 MediaPool refactoring.
2026-04-02 Clean-up. Removed CameraPlayer.
2026-04-02 MediaPool updates all filelists (shaders, videos) in background thread.
2026-04-07 Added DirectoryCache (WIP).
2026-04-07 Fixed/added copyright notices.
2026-04-07 added 'terminus' as main font; rework of UI
2026-04-08 Directories for video file selection.
2026-04-09 Added PreviewCache.
2026-04-10 Staging (WIP).
2026-04-10 Previews now show up on first hover.
2026-04-10 Preview scrubbing does not stall video playback anymore.
2026-04-11 added uniforms to shaders
2026-04-13 MenuSystem clean-up. Using new structs.
2026-04-13 CleanUp MenuSystem and UI; Reworked PlanePreviewWidget
2026-04-16 implemented "new folder" option
2026-04-16 "new folder" dialog UI changes
2026-04-17 implemented file-renaming; creating new folders works in sub-folderes now
2026-04-21 Set iTime on plane shader.
2026-04-21 FileManager (WIP)
2026-04-21 Fixed? Clear frame/close pop-up on edit menu change.
2026-04-26 UI: default value for fx (WIP); shortcut for SRC-menu (WIP), cosmetic changes;
2026-04-27 Fixed focus index bug. Optimized preview cache.
2026-04-27 Focusing active video file.
2026-04-28 Focusing active video file works.
2026-04-28 IntSpinBox supports option names. Switching to active media slot on plane change.
2026-04-29 Context menu opens on ValueChangeEvent::Type::Up (Keyboard Control).
2026-04-29 Fixed several issues when moving media slots to a different plane.
2026-04-29 Plane-Change for Live-Input and Shaders; Stop selecting new Plane-Preview when plane count limits reached
2026-04-30 InfoMenu shows active (playing) media. Same menu layout for all other menus.
2026-05-01 VM-1 Device: added all analog inputs with a basic filter; bug-fix in i2c receiver-callback; re-writing ButtonState from Enum to Bitmask (wip)
2026-05-01 VM-1-Device ButtonStates as bitmask (wip)
2026-05-01 removed m_mediaSlotIdToPlayerId.clear(); from PlaybackOperator
2026-05-01 Highlight active SRC.
2026-05-01 VM-1 Device rework: using bitmask instead of buttonstate-enum
2026-05-01 centralized media button and bank management in registry
2026-05-04 Changed builddir to build.
2026-05-05 Show TinyFileManager QR-Code.
2026-05-05 Added analog uniforms.
2026-05-05 Added install script for arduino-cli.
2026-05-18 Added in-out points.
2026-05-18 More in-out point.
2026-05-28 added seed to fragments shader
2026-06-01 removed plane change on SRC/CTL
2026-06-01 Shader parameters update bug fixed.
2026-06-01 Modified VM-1 Basic keyboard controls (WIP)
2026-06-03 Keyboard modifications: SRC on key 1
2026-06-08 Settings Menu Clean Up; PopUp Message not clearing whole screen; converted glm::vec2 to uvec2 in StbRenderer; default looping=true in Registry.h
2026-06-09 fixed mediaPreview position in src menu
2026-06-09 added BlendMode 'Add' - still WIP, the shader needs some re-work (turns white when opacity is lowered)
2026-06-10 (WIP) FileManager - update changed filenames on mediaSlots
2026-06-11 Added currentPts to VideoInputConfig in Registry.
2026-06-11 Added reset and vec2 support for shader parameters.
2026-06-12 added 'pause'-function in CTL menu for videos
2026-06-16 fixed 'pause'-function with m_pauseStartTime
2026-06-16 changed currentFrame to currentTime (all time values stored in seconds as double); fixed out-point bug; time values in UI are displayed as smpte; added SpinBoxSeconds;
2026-06-16 fixed bug with m_currentTime
